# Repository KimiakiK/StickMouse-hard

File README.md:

# Stick Mouse
[Software](https://github.com/KimiakiK/StickMouse-soft)

# Features
- ジョイスティックと静音スイッチを備えたスティック型のマウス
- マウスポインタの移動とスクロールをジョイスティックで操作（ジョイスティック押し込みで切り替え）
- 左クリックと右クリック

# Major Components  
- STM32F042K6
- Joystick
- Kailh ミュートマイクロスイッチ

# Photos

## PCB
- V1.1

- V1.0

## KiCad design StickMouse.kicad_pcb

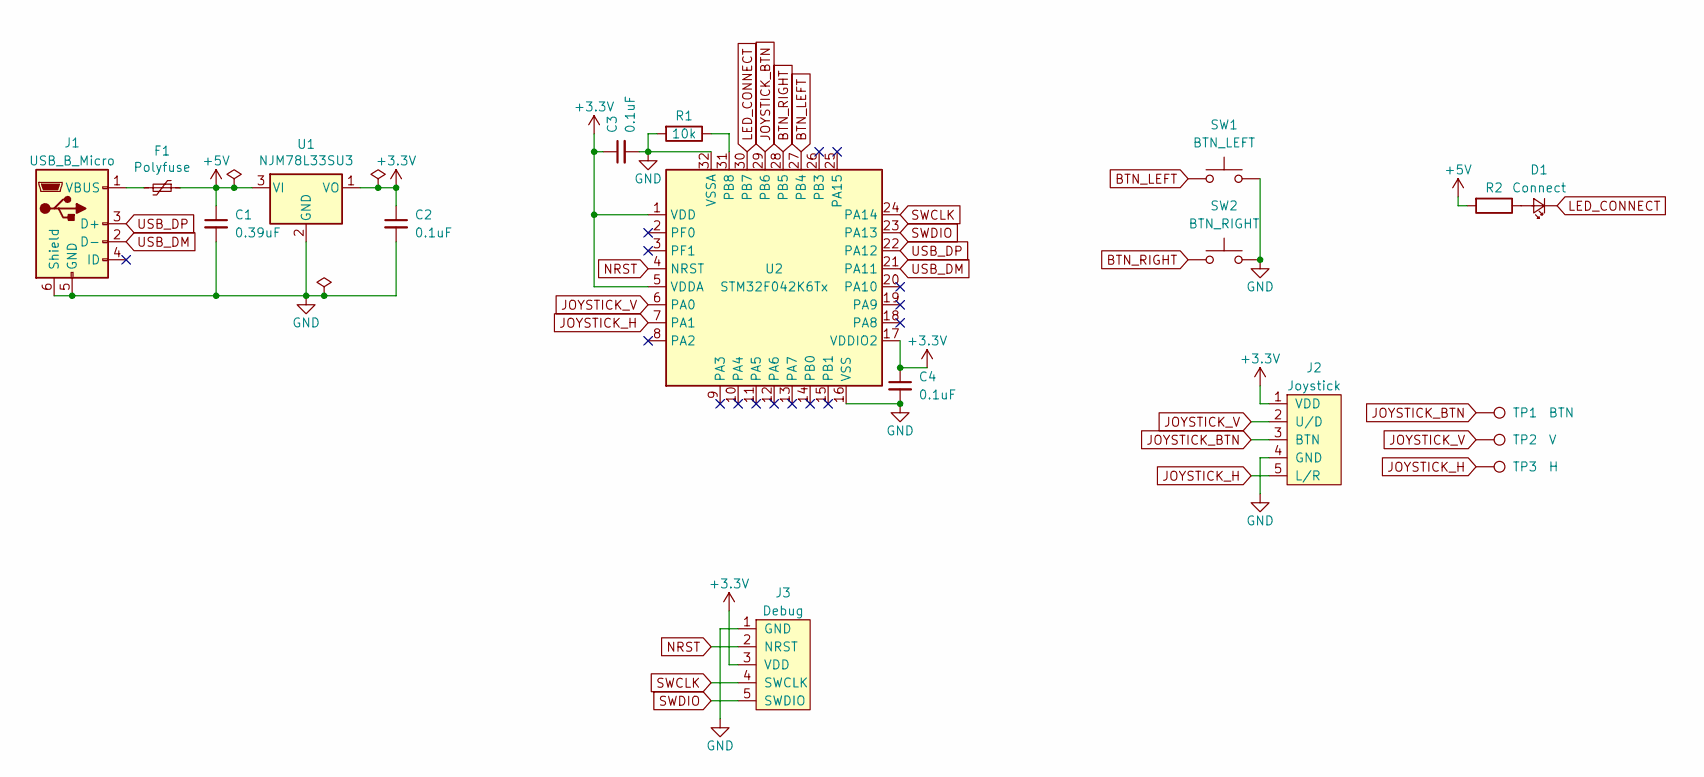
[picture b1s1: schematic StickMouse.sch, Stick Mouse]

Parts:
C1: 0.39uF; C_0603_1608Metric_Pad1.05x0.95mm_HandSolder
C2, C3, C4: 0.1uF; C_0603_1608Metric_Pad1.05x0.95mm_HandSolder
D1: Connect; LED_0603_1608Metric_Pad1.05x0.95mm_HandSolder
F1: Polyfuse; Fuse_1206_3216Metric_Pad1.42x1.75mm_HandSolder
J1: USB_B_Micro; ZX62-B-5PA
J2: Joystick; JoyCon_Joystick
J3: Debug; STM32_Debug_5pin
R1: 10k; R_0603_1608Metric_Pad1.05x0.95mm_HandSolder
R2: R; R_0603_1608Metric_Pad1.05x0.95mm_HandSolder
SW1: BTN_LEFT; Kailh_Mute_Switch
SW2: BTN_RIGHT; Kailh_Mute_Switch
TP1: BTN; TestPoint_Pad_1.0x1.0mm
TP2: V; TestPoint_Pad_1.0x1.0mm
TP3: H; TestPoint_Pad_1.0x1.0mm
U1: NJM78L33SU3; SOT-89-3
U2: STM32F042K6Tx; LQFP-32_7x7mm_P0.8mm_FusionPCB

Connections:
+3V3: C2.1, C3.1, C4.1, J2.1 (VDD), J3.3 (VDD), U1.1 (VO), U2.1 (VDD), U2.5 (VDDA), U2.17 (VDDIO2)
+5V: C1.1, F1.1, R2.2, U1.3 (VI)
BTN_LEFT: SW1.1, U2.27 (PB4)
BTN_RIGHT: SW2.1, U2.28 (PB5)
GND: C1.2, C2.2, C3.2, C4.2, J1.5 (GND), J1.6 (Shield), J2.4 (GND), J3.1 (GND), R1.2, SW1.2, SW2.2, U1.2 (GND), U2.16 (VSS), U2.32 (VSSA)
JOYSTICK_BTN: J2.3 (BTN), TP1.1, U2.29 (PB6)
JOYSTICK_H: J2.5 (L/R), TP3.1, U2.7 (PA1)
JOYSTICK_V: J2.2 (U/D), TP2.1, U2.6 (PA0)
LED_CONNECT: D1.1 (K), U2.30 (PB7)
NRST: J3.2 (NRST), U2.4 (NRST)
unnamed: D1.2 (A), R2.1
unnamed: F1.2, J1.1 (VBUS)
unnamed: R1.1, U2.31 (PB8)
SWCLK: J3.4 (SWCLK), U2.24 (PA14)
SWDIO: J3.5 (SWDIO), U2.23 (PA13)
USB_DM: J1.2 (D-), U2.21 (PA11)
USB_DP: J1.3 (D+), U2.22 (PA12)

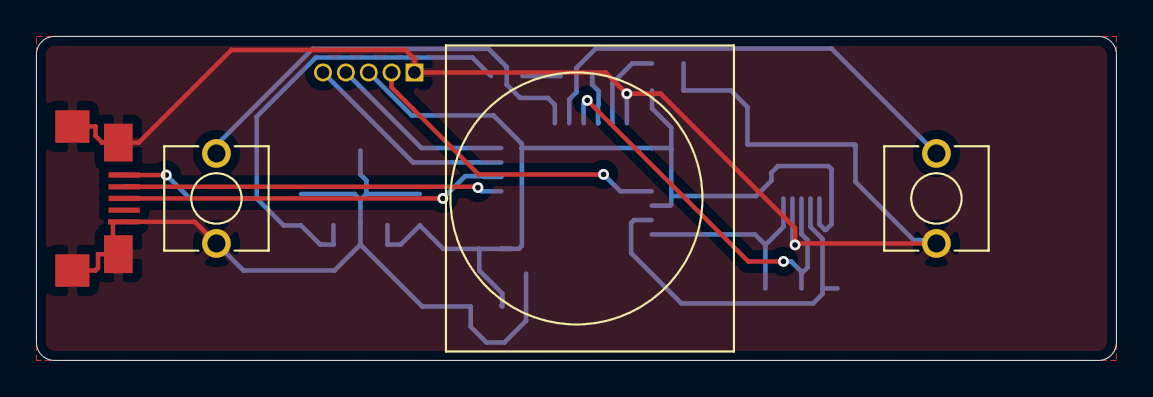
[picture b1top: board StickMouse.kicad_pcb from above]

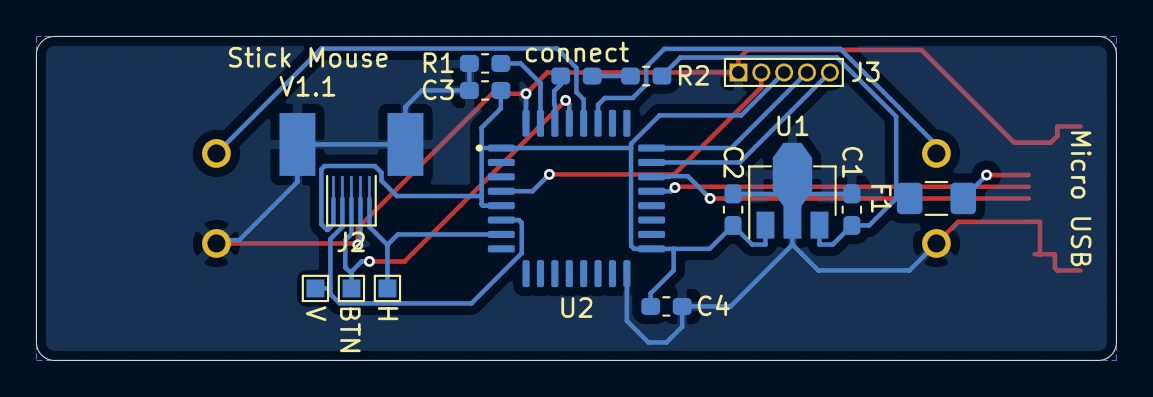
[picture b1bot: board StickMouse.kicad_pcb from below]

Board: 2 copper layers, 60.0 x 18.0 mm, 18 parts (14 on the bottom side), 17 nets.

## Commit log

2021-02-10 基板 V1.0
2021-03-21 基板 V1.1
2021-04-29 Add images
